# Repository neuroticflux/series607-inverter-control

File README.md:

# series607-inverter-control

### Overview
#### What is this?
The Series607 Inverter Control is an Arduino-based device providing data logging and remote control of a Series 607 inverter (Found in Sweden at Kjell &amp; Co under the brand LuxorParts).
The Series 607 comes with a wired control panel showing power draw on the AC side and voltage on the DC side. The device described in this repository hijacks the communication bus going to the control panel and decodes the data, then reports it via Modbus to a master device, such as a Victron Cerbo GX, or a Raspberry Pi running VenusOS. It even lets you remotely turn the inverter on or off from the touch menu, and reports alarms and fault codes like undervoltage, overvoltage, overheating etc. :)

#### Disclaimer
If you want to try this out with your own Series 607 inverter, feel free! Of course I take no responsibility for what happens to you or your hardware if you use any material or information provided in this repository. You should always be careful around high voltages and high currents. There is NO NEED to get anywhere near the AC side outlets while building this project, and there is ABSOLUTELY NO NEED to open up the inverter itself.

#### RJ12 cable pinout:
Both the pinout and color codes may very well be different on different units, so always double-check before you plug in your expensive equipment that you have your wires hooked up right!

- PIN1 (blue): power switch
- PIN2 (black): +12V
- PIN3 (red): GND
- PIN4 (green): DATA
- PIN5 (yellow): CS
- PIN6 (brown): CLK

### Instructions

#### Hardware
You need an Arduino (I've tested on Uno and the prototype runs on a Micro, likely any ATmega328-based board will work) and some RS232-to-USB bridge like an FTDI breakout board or dongle. It needs to show up in VenusOS as /dev/ttyUSB*, so using the built-in USB port on the Arduinos doesn't work. If anyone can figure out how to set VenusOS up so it scans /dev/ttyACM* as well, please let me know. :)

You also need one PNP and one NPN transistor - 2N3904 and 2N3906 work fine - and two 10kohm resistors. There's a schematic under /pcb but it's not up to date. Check the Falstad link below for a schematic of the high side switch circuit you need for remote on/off switching in VenusOS to work, the rest should be fairly self-explanatory. Pin 1 (power switch) goes to the collector of the PNP, Pin 2 (+12V) goes to the emitter.
Pins 4, 5, and 6 go to the SPI MOSI, CS and CLK pins on the Arduino, and Arduino Pin 4 goes to the base of the NPN.
If you have an Arduino Micro, you can use the hardware serial port to interface with the FTDI board. The sketch in the repo is already set up for that. If you have a Uno or some other Arduino-style board, you might need to alter the code to set up a SoftwareSerial port on two of the digital pins and connect those to the FTDI.

The circuit is simple enough to deadbug, or stick it on a protoboard with fancy pin headers if you want. :)
Burn the sketch to the Arduino and connect it to the inverter according to the pinout.

DON'T GET +12V NEAR THE GPIO LINES! It will fry your microcontroller. Yes, it's happened to me, more than once. :P

#### VenusOS
Make sure you have superuser access to your Victron device, and a way to get files onto it (wget works fine I guess).
Put the series607.py script in /opt/victronenergy/dbus-modbus-client/, then edit the dbus-modbus-client.py script in that same folder. Add this line to the list of imports:
```Python
import series607
```
Now, when you connect the interface using the RS232 dongle, a new device called 'Series607 FSW Inverter' should show up in your VenusOS menu. It may take a minute for the TTY poller to run, so be patient. ;)

If you've gotten the pinout and high-side switch right, you should now be able to control your inverter and get DC-side voltage and AC-side power showing up.

### Technical

Simulating the high side BJT switch circuit in Falstad:
https://tinyurl.com/24upg6vq

TODO: Schematics/images

### Compatibility
I've only been able to find these inverters here in Sweden, but I'd love to know if there are similar products out there with the same or similar connectivity that could be hacked in this way. Feel free to post an issue if you have a question or can provide information, or a pull request if you have something to add like code or revised/improved hardware.

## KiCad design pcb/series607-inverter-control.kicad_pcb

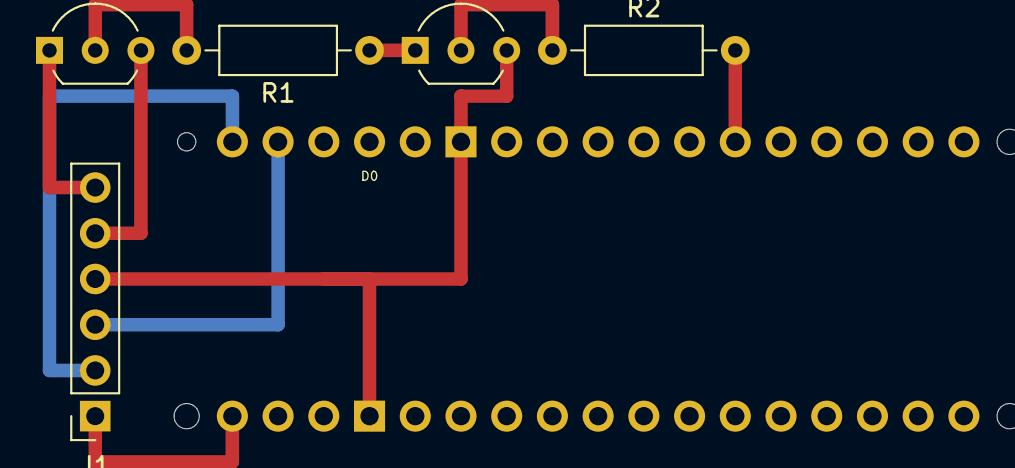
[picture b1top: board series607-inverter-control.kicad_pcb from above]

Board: 2 copper layers, 6 parts (1 on the bottom side), 10 nets.

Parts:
A1: Arduino_Micro_Socket
J1: Conn_01x06_Pin; PinSocket_1x06_P2.54mm_Vertical
Q1: 2N3904; TO-92_Inline_Wide
Q2: 2N3906; TO-92_Inline_Wide
R1, R2: 10k; R_Axial_DIN0207_L6.3mm_D2.5mm_P10.16mm_Horizontal

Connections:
Arduino_GND: A1.GND1 (GND), A1.GND2 (GND), J1.4, Q1.3 (C)
Arduino_Pin_7: A1.D7 (D7_INT4), R2.2
Arduino_Pin_10: A1.SS (SPI_CS), J1.3
Arduino_Pin_11: A1.MOSI (SPI_MOSI), J1.2
Arduino_Pin_13: A1.SCK (SPI_SCK), J1.1
unnamed: J1.5, Q2.3 (C)
unnamed: J1.6, Q2.1 (E)
unnamed: Q1.2 (B), R2.1
unnamed: Q1.1 (E), R1.1
unnamed: Q2.2 (B), R1.2

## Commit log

2023-08-13 Added sketch
2023-08-13 Added KiCad protoboard project
2023-08-14 Added Python script for VenusOS
2023-08-14 ModbusRTU and Victron VenusOS support
2023-08-17 Changes to support Arduino Micro
2023-08-18 Added alarms, more correct values
2023-08-18 Device firmware supports alarms
2023-08-18 Correct power multiplier
